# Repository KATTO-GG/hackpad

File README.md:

# hackpad
4-key macropad with rotary encoder, built for Hack Club's Hackpad program. :)
Features
4 mechanical switches (WASD-style layout, direct-wired to XIAO RP2040, no diode matrix)
Rotary encoder (volume up/down)
Seeed XIAO RP2040 as controller
Firmware: KMK (CircuitPython-based)
Case: 3D printed, [X]-part design (case + cover)
a repo for my custom hackpad for hackclub
here is a photo of the pcb

here is a photo ofd the schematic

picture of case

BOM
Part	Qty	Link
Seeed XIAO RP2040	1	https://www.seeedstudio.com/XIAO-RP2040-v1-0-p-5026.html
Mechanical switch (Cherry MX or clone)	4	
Keycap	4	
Rotary encoder (EC11)	1	
M2 screws (case assembly)	[qty]	
PCB (self-fabbed via gerbers.zip)	1
uwu

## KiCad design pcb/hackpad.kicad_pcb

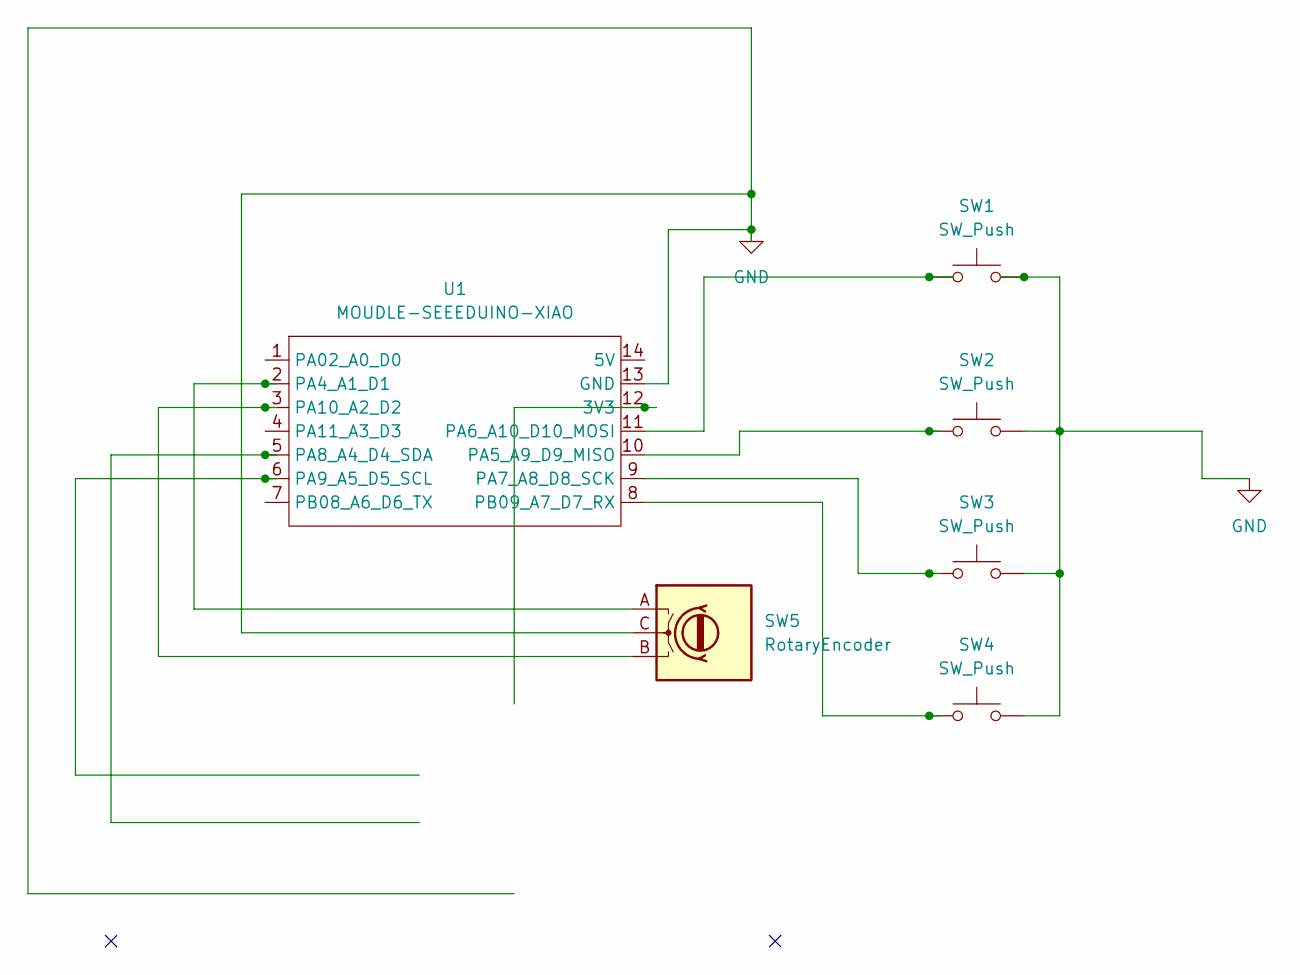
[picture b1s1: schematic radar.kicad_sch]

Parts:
SW1, SW2, SW3, SW4: SW_Push; SW_Cherry_MX_1.00u_PCB
SW5: RotaryEncoder; RotaryEncoder_Alps_EC11E_Vertical_H20mm
U1: MOUDLE-SEEEDUINO-XIAO; XIAO-Generic-Hybrid-14P-2.54-21X17.8MM

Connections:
GND: SW1.2, SW2.2, SW3.2, SW4.2, SW5.C, U1.13 (GND)
unnamed: SW5.A, U1.2 (PA4_A1_D1)
unnamed: SW2.1, U1.10 (PA5_A9_D9_MISO)
unnamed: SW1.1, U1.11 (PA6_A10_D10_MOSI)
unnamed: SW3.1, U1.9 (PA7_A8_D8_SCK)
unnamed: SW5.B, U1.3 (PA10_A2_D2)
unnamed: SW4.1, U1.8 (PB09_A7_D7_RX)

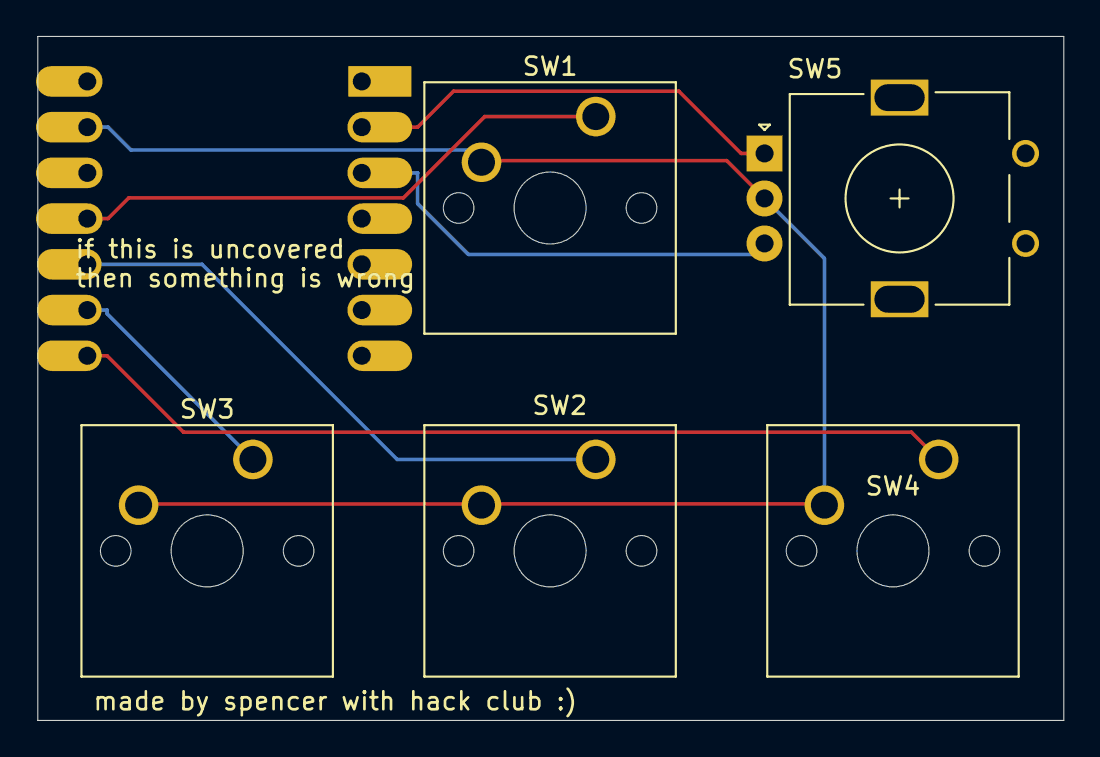
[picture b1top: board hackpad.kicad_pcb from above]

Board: 2 copper layers, 57.0 x 38.0 mm, 6 parts (1 on the bottom side), 7 nets.
